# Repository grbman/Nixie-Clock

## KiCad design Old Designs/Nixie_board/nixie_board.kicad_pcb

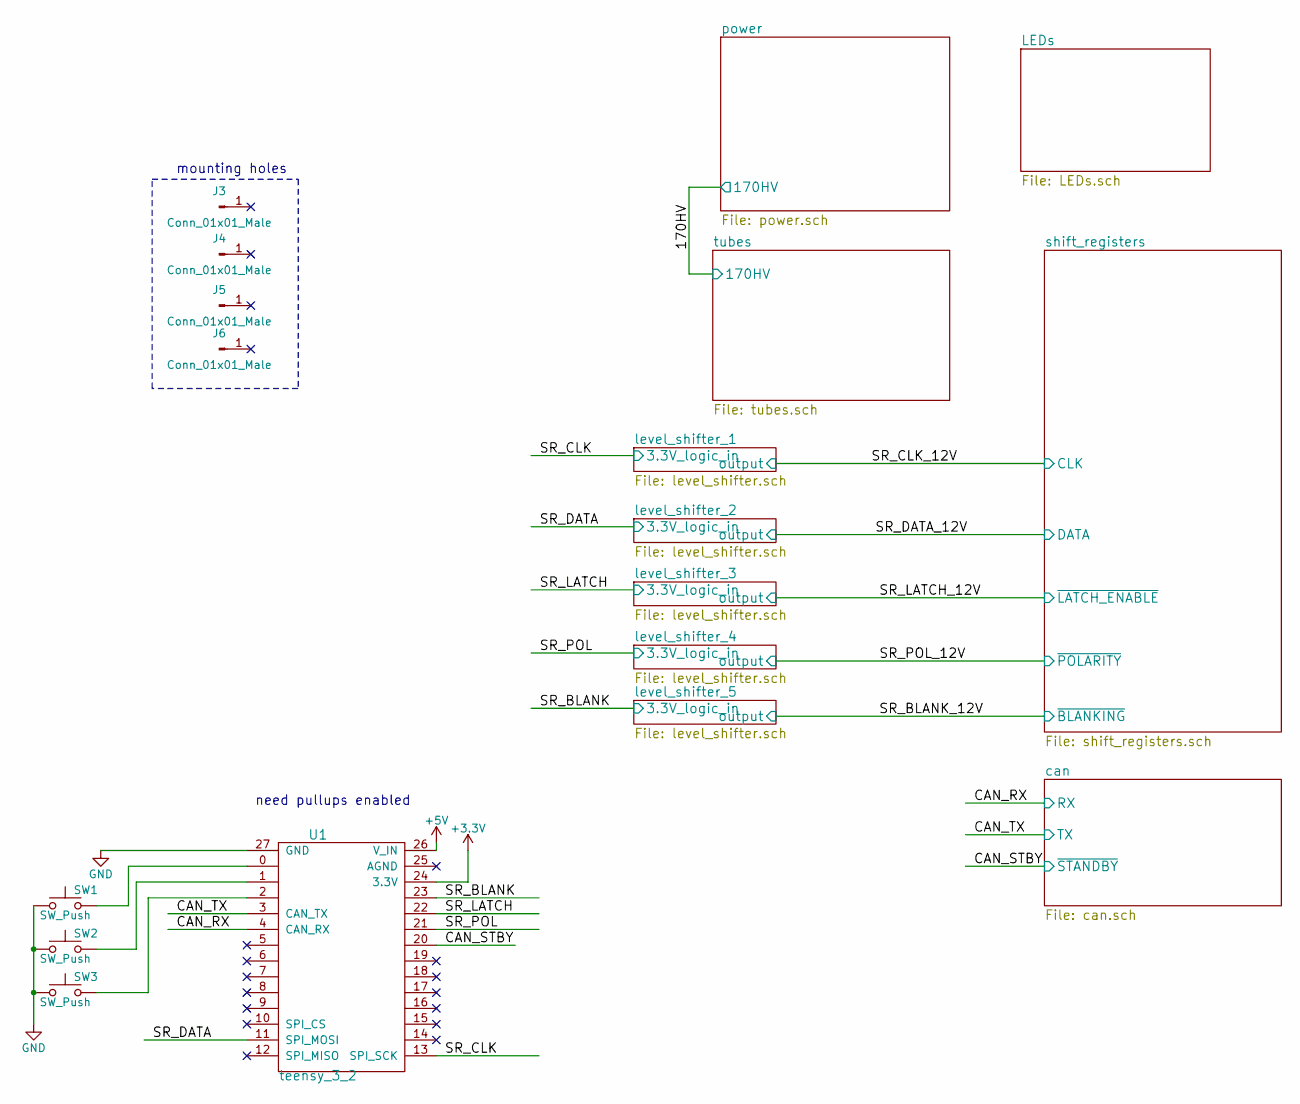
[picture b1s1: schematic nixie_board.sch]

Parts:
J3, J4, J5, J6: Conn_01x01_Male; MountingHole_3.2mm_M3_DIN965_Pad
SW1, SW2, SW3: SW_Push; SW_PUSH_6mm
U1: teensy_3_2; teensy_3.2

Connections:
+3V3: U1.24 (3.3V); also elsewhere on the board
+5V: U1.26 (V_IN); also elsewhere on the board
/CAN_RX: U1.4 (CAN_RX); also elsewhere on the board
/CAN_STBY: U1.20; also elsewhere on the board
/CAN_TX: U1.3 (CAN_TX); also elsewhere on the board
/SR_BLANK: U1.23; also elsewhere on the board
/SR_CLK: U1.13 (SPI_SCK); also elsewhere on the board
/SR_DATA: U1.11 (SPI_MOSI); also elsewhere on the board
/SR_LATCH: U1.22; also elsewhere on the board
/SR_POL: U1.21; also elsewhere on the board
GND: SW1.1, SW2.1, SW3.1, U1.27 (GND); also elsewhere on the board
unnamed: SW1.2, U1.0
unnamed: SW2.2, U1.1
unnamed: SW3.2, U1.2

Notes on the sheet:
need pullups enabled
mounting holes

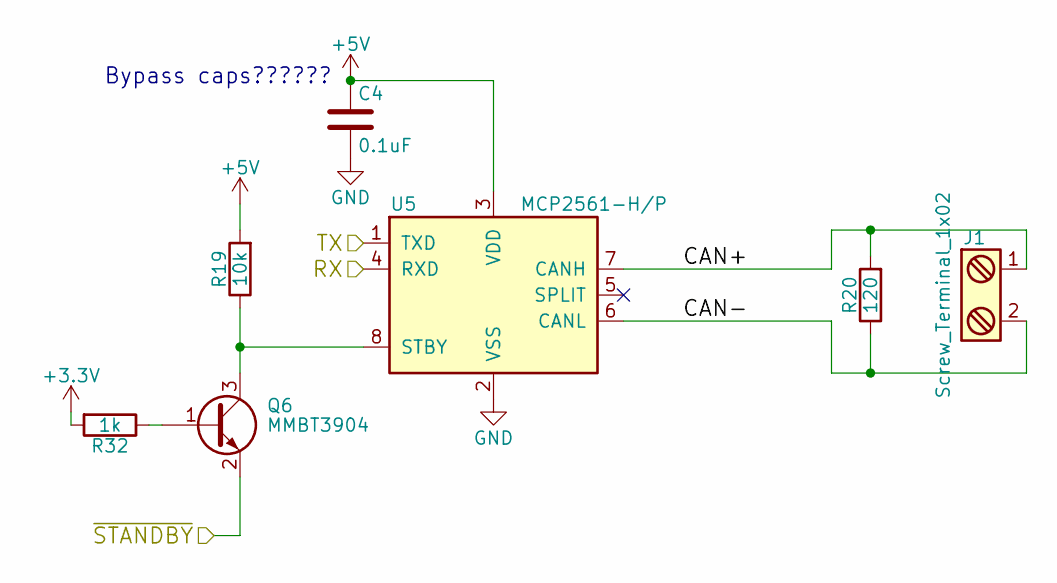
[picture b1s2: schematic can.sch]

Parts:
C4: 0.1uF; C_0603_HandSoldering
J1: Screw_Terminal_1x02; TerminalBlock_Pheonix_PT-3.5mm_2pol
Q6: MMBT3904; SOT-23
R19: 10k; R_0603_HandSoldering
R20: 120; R_0603_HandSoldering
R32: 1k; R_0603_HandSoldering
U5: MCP2561-H/P; DIP-8_W7.62mm

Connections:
+3V3: R32.2; also elsewhere on the board
+5V: C4.1, R19.2, U5.3 (VDD); also elsewhere on the board
/CAN_RX: U5.4 (RXD); also elsewhere on the board
/CAN_STBY: Q6.2 (E); also elsewhere on the board
/CAN_TX: U5.1 (TXD); also elsewhere on the board
/can/CAN+: J1.1, R20.2, U5.7 (CANH)
/can/CAN-: J1.2, R20.1, U5.6 (CANL)
GND: C4.2, U5.2 (VSS); also elsewhere on the board
unnamed: Q6.1 (B), R32.1
unnamed: Q6.3 (C), R19.1, U5.8 (STBY)

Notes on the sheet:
Bypass caps??????

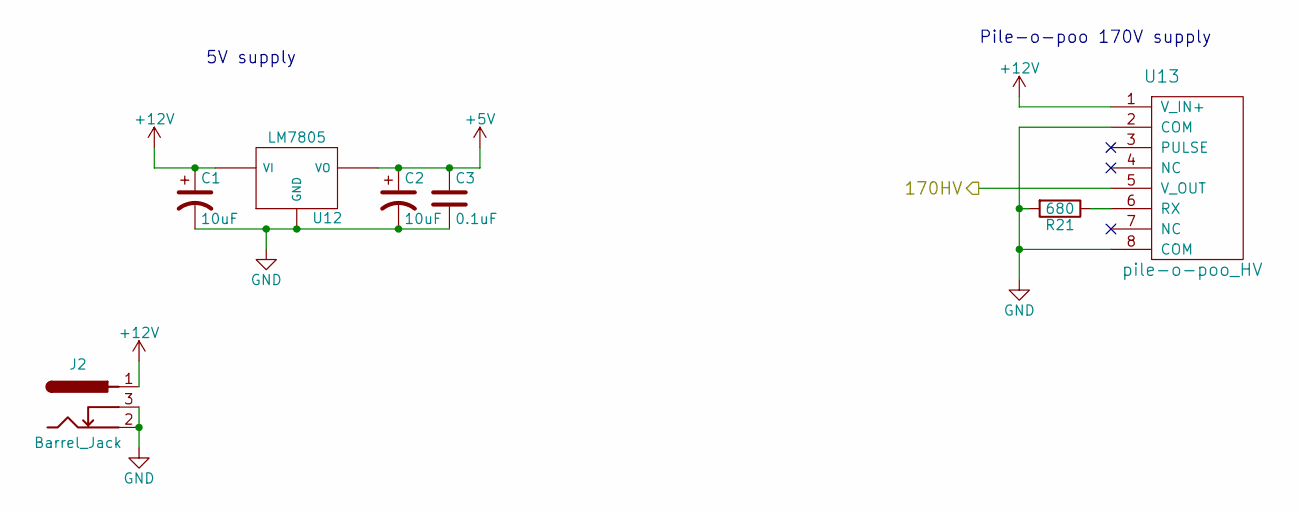
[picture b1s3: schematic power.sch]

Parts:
C1, C2: 10uF; CP_Radial_D5.0mm_P2.00mm
C3: 0.1uF; C_0603_HandSoldering
J2: Barrel_Jack; barrel_jack
R21: 680; R_0603_HandSoldering
U12: LM7805; TO-220
U13: pile-o-poo_HV; pile_o_poo

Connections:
+5V: C2.1, C3.1, U12.3 (VO); also elsewhere on the board
+12V: C1.1, J2.1, U12.1 (VI), U13.1 (V_IN+); also elsewhere on the board
/170HV: U13.5 (V_OUT); also elsewhere on the board
GND: C1.2, C2.2, C3.2, J2.2, J2.3, R21.2, U12.2 (GND), U13.2 (COM), U13.8 (COM); also elsewhere on the board
unnamed: R21.1, U13.6 (RX)

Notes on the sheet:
5V supply
Pile-o-poo 170V supply

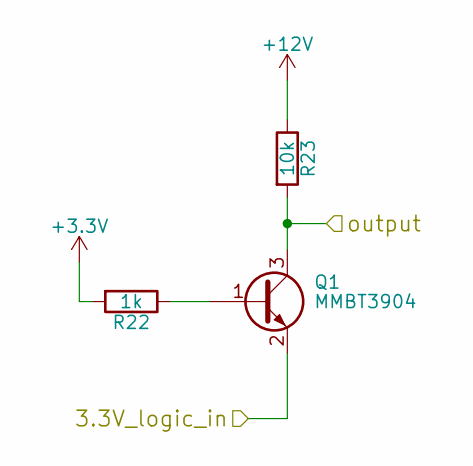
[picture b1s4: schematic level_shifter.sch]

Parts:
Q4: MMBT3904; SOT-23
R24: 1k; R_0603_HandSoldering
R25: 10k; R_0603_HandSoldering

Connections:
+3V3: R24.2; also elsewhere on the board
+12V: R25.1; also elsewhere on the board
/SR_POL: Q4.2 (E); also elsewhere on the board

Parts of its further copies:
Q1, Q2, Q3, Q5: MMBT3904; SOT-23
R22, R26, R28, R30: 1k; R_0603_HandSoldering
R23, R27, R29, R31: 10k; R_0603_HandSoldering

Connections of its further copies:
+3V3: R22.2, R26.2, R28.2, R30.2; also elsewhere on the board
+12V: R23.1, R27.1, R29.1, R31.1; also elsewhere on the board
/SR_BLANK: Q5.2 (E); also elsewhere on the board
/SR_BLANK_12V: Q5.3 (C), R31.2; also elsewhere on the board
/SR_CLK: Q1.2 (E); also elsewhere on the board
/SR_CLK_12V: Q1.3 (C), R23.2; also elsewhere on the board
/SR_DATA: Q2.2 (E); also elsewhere on the board
/SR_LATCH: Q3.2 (E); also elsewhere on the board
/SR_LATCH_12V: Q3.3 (C), R27.2; also elsewhere on the board
unnamed: Q1.1 (B), R22.1
unnamed: Q3.1 (B), R26.1
unnamed: Q5.1 (B), R30.1

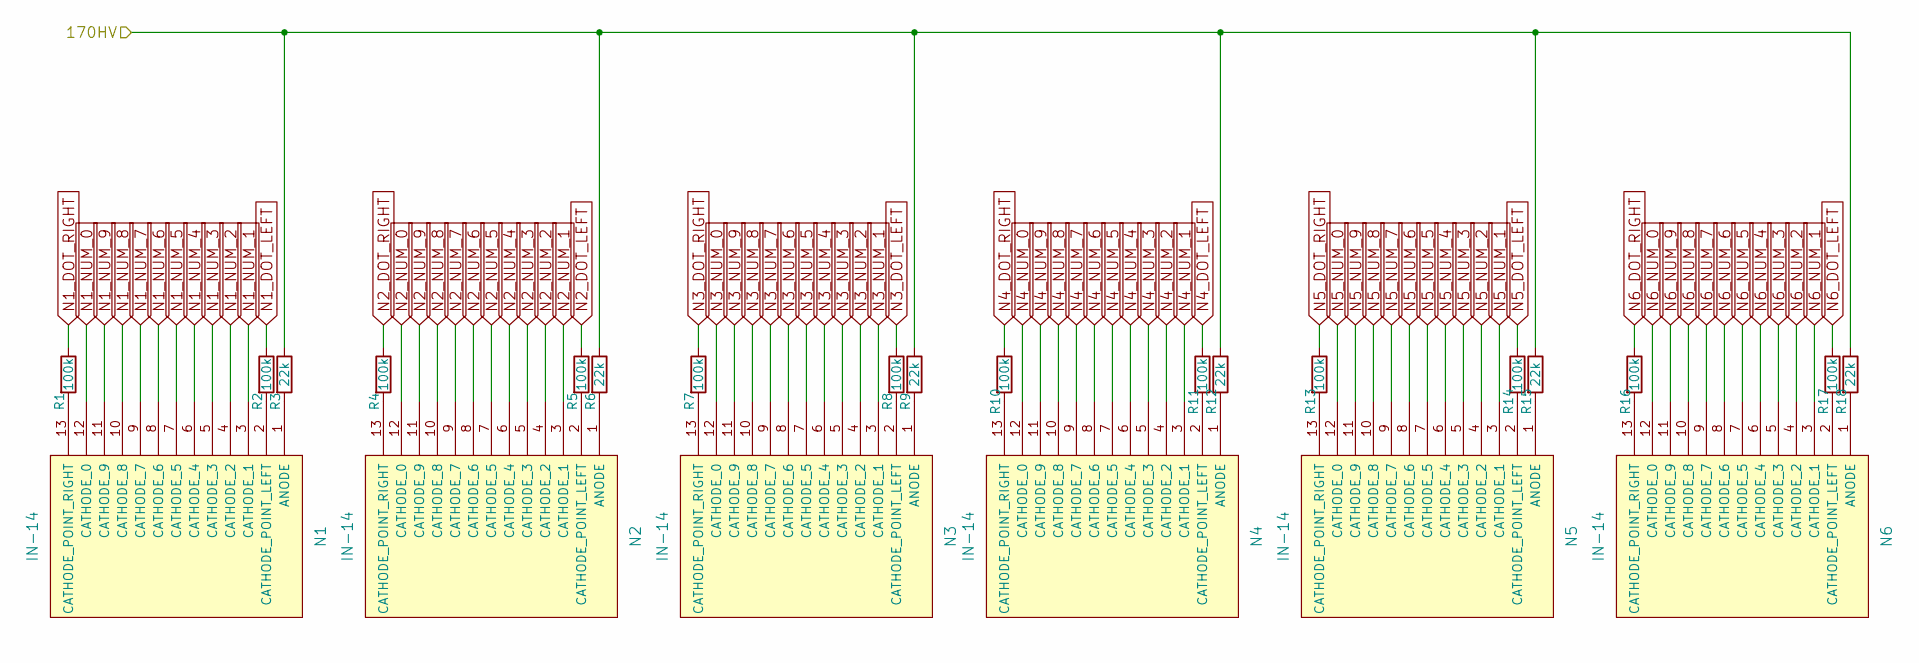
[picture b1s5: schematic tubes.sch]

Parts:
N1, N2, N3, N4, N5, N6: IN-14; in-14
R1, R2, R4, R5, R7, R8, R10, R11, R13, R14, R16, R17: 100k; R_0603_HandSoldering
R3, R6, R9, R12, R15, R18: 22k; R_0603_HandSoldering

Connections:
/170HV: R3.1, R6.1, R9.1, R12.1, R15.1, R18.1; also elsewhere on the board
N1_DOT_LEFT: R2.1; also elsewhere on the board
N1_DOT_RIGHT: R1.1; also elsewhere on the board
N1_NUM_0: N1.12 (CATHODE_0); also elsewhere on the board
N1_NUM_1: N1.3 (CATHODE_1); also elsewhere on the board
N1_NUM_2: N1.4 (CATHODE_2); also elsewhere on the board
N1_NUM_3: N1.5 (CATHODE_3); also elsewhere on the board
N1_NUM_4: N1.6 (CATHODE_4); also elsewhere on the board
N1_NUM_5: N1.7 (CATHODE_5); also elsewhere on the board
N1_NUM_6: N1.8 (CATHODE_6); also elsewhere on the board
N1_NUM_7: N1.9 (CATHODE_7); also elsewhere on the board
N1_NUM_8: N1.10 (CATHODE_8); also elsewhere on the board
N1_NUM_9: N1.11 (CATHODE_9); also elsewhere on the board
N2_DOT_LEFT: R5.1; also elsewhere on the board
N2_DOT_RIGHT: R4.1; also elsewhere on the board
N2_NUM_0: N2.12 (CATHODE_0); also elsewhere on the board
N2_NUM_1: N2.3 (CATHODE_1); also elsewhere on the board
N2_NUM_2: N2.4 (CATHODE_2); also elsewhere on the board
N2_NUM_3: N2.5 (CATHODE_3); also elsewhere on the board
N2_NUM_4: N2.6 (CATHODE_4); also elsewhere on the board
N2_NUM_5: N2.7 (CATHODE_5); also elsewhere on the board
N2_NUM_6: N2.8 (CATHODE_6); also elsewhere on the board
N2_NUM_7: N2.9 (CATHODE_7); also elsewhere on the board
N2_NUM_8: N2.10 (CATHODE_8); also elsewhere on the board
N2_NUM_9: N2.11 (CATHODE_9); also elsewhere on the board
N3_DOT_LEFT: R8.1; also elsewhere on the board
N3_DOT_RIGHT: R7.1; also elsewhere on the board
N3_NUM_0: N3.12 (CATHODE_0); also elsewhere on the board
N3_NUM_1: N3.3 (CATHODE_1); also elsewhere on the board
N3_NUM_2: N3.4 (CATHODE_2); also elsewhere on the board
N3_NUM_3: N3.5 (CATHODE_3); also elsewhere on the board
N3_NUM_4: N3.6 (CATHODE_4); also elsewhere on the board
N3_NUM_5: N3.7 (CATHODE_5); also elsewhere on the board
N3_NUM_6: N3.8 (CATHODE_6); also elsewhere on the board
N3_NUM_7: N3.9 (CATHODE_7); also elsewhere on the board
N3_NUM_8: N3.10 (CATHODE_8); also elsewhere on the board
N3_NUM_9: N3.11 (CATHODE_9); also elsewhere on the board
N4_DOT_LEFT: R11.1; also elsewhere on the board
N4_DOT_RIGHT: R10.1; also elsewhere on the board
N4_NUM_0: N4.12 (CATHODE_0); also elsewhere on the board
N4_NUM_1: N4.3 (CATHODE_1); also elsewhere on the board
N4_NUM_2: N4.4 (CATHODE_2); also elsewhere on the board
N4_NUM_3: N4.5 (CATHODE_3); also elsewhere on the board
N4_NUM_4: N4.6 (CATHODE_4); also elsewhere on the board
N4_NUM_5: N4.7 (CATHODE_5); also elsewhere on the board
N4_NUM_6: N4.8 (CATHODE_6); also elsewhere on the board
N4_NUM_7: N4.9 (CATHODE_7); also elsewhere on the board
N4_NUM_8: N4.10 (CATHODE_8); also elsewhere on the board
N4_NUM_9: N4.11 (CATHODE_9); also elsewhere on the board
N5_DOT_LEFT: R14.1; also elsewhere on the board
N5_DOT_RIGHT: R13.1; also elsewhere on the board
N5_NUM_0: N5.12 (CATHODE_0); also elsewhere on the board
N5_NUM_1: N5.3 (CATHODE_1); also elsewhere on the board
N5_NUM_2: N5.4 (CATHODE_2); also elsewhere on the board
N5_NUM_3: N5.5 (CATHODE_3); also elsewhere on the board
N5_NUM_4: N5.6 (CATHODE_4); also elsewhere on the board
N5_NUM_5: N5.7 (CATHODE_5); also elsewhere on the board
N5_NUM_6: N5.8 (CATHODE_6); also elsewhere on the board
N5_NUM_7: N5.9 (CATHODE_7); also elsewhere on the board
N5_NUM_8: N5.10 (CATHODE_8); also elsewhere on the board
N5_NUM_9: N5.11 (CATHODE_9); also elsewhere on the board
N6_DOT_LEFT: R17.1; also elsewhere on the board
N6_DOT_RIGHT: R16.1; also elsewhere on the board
N6_NUM_0: N6.12 (CATHODE_0); also elsewhere on the board
N6_NUM_1: N6.3 (CATHODE_1); also elsewhere on the board
N6_NUM_2: N6.4 (CATHODE_2); also elsewhere on the board
N6_NUM_3: N6.5 (CATHODE_3); also elsewhere on the board
N6_NUM_4: N6.6 (CATHODE_4); also elsewhere on the board
N6_NUM_5: N6.7 (CATHODE_5); also elsewhere on the board
N6_NUM_6: N6.8 (CATHODE_6); also elsewhere on the board
N6_NUM_7: N6.9 (CATHODE_7); also elsewhere on the board
N6_NUM_8: N6.10 (CATHODE_8); also elsewhere on the board
N6_NUM_9: N6.11 (CATHODE_9); also elsewhere on the board
unnamed: N1.1 (ANODE), R3.2
unnamed: N1.2 (CATHODE_POINT_LEFT), R2.2
unnamed: N1.13 (CATHODE_POINT_RIGHT), R1.2
unnamed: N2.1 (ANODE), R6.2
unnamed: N2.2 (CATHODE_POINT_LEFT), R5.2
unnamed: N2.13 (CATHODE_POINT_RIGHT), R4.2
unnamed: N3.1 (ANODE), R9.2
unnamed: N3.2 (CATHODE_POINT_LEFT), R8.2
unnamed: N3.13 (CATHODE_POINT_RIGHT), R7.2
unnamed: N4.1 (ANODE), R12.2
unnamed: N4.2 (CATHODE_POINT_LEFT), R11.2
unnamed: N4.13 (CATHODE_POINT_RIGHT), R10.2
unnamed: N5.1 (ANODE), R15.2
unnamed: N5.2 (CATHODE_POINT_LEFT), R14.2
unnamed: N5.13 (CATHODE_POINT_RIGHT), R13.2
unnamed: N6.1 (ANODE), R18.2
unnamed: N6.2 (CATHODE_POINT_LEFT), R17.2
unnamed: N6.13 (CATHODE_POINT_RIGHT), R16.2

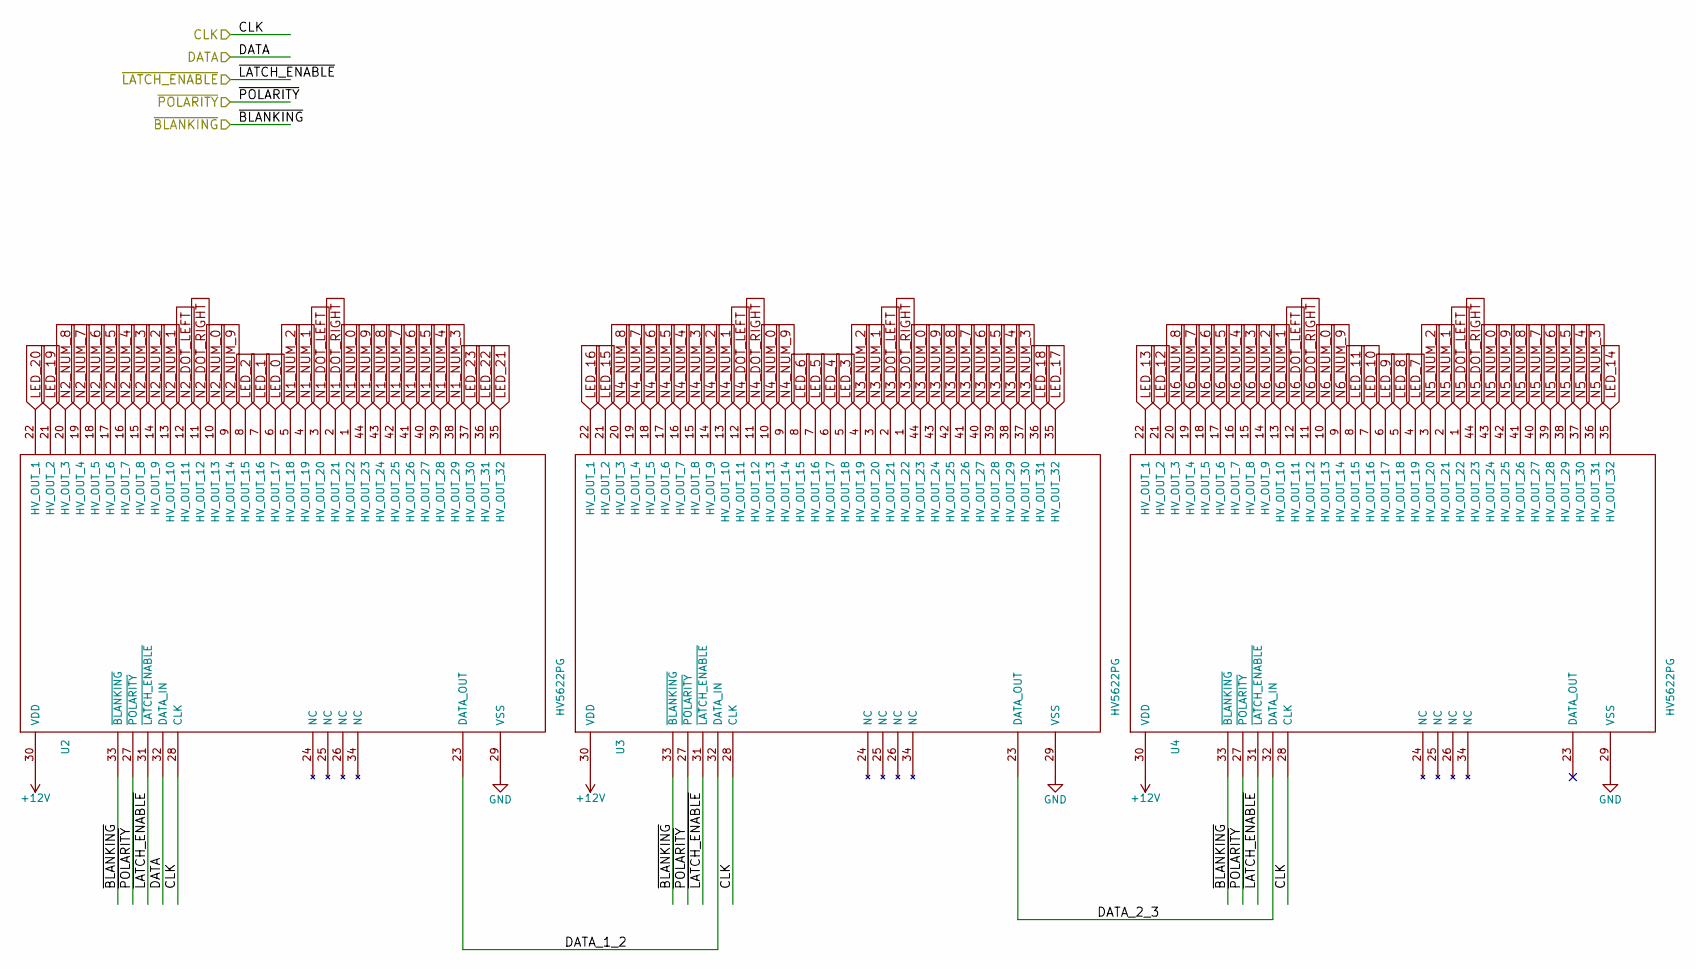
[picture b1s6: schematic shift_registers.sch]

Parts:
U2, U3, U4: HV5622PG; LQFP-44_Gullwing

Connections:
+12V: U2.30 (VDD), U3.30 (VDD), U4.30 (VDD); also elsewhere on the board
/SR_BLANK_12V: U2.33 (~BLANKING), U3.33 (~BLANKING), U4.33 (~BLANKING); also elsewhere on the board
/SR_CLK_12V: U2.28 (CLK), U3.28 (CLK), U4.28 (CLK); also elsewhere on the board
/SR_LATCH_12V: U2.31 (~LATCH_ENABLE), U3.31 (~LATCH_ENABLE), U4.31 (~LATCH_ENABLE); also elsewhere on the board
/shift_registers/DATA_1_2: U2.23 (DATA_OUT), U3.32 (DATA_IN)
/shift_registers/DATA_2_3: U3.23 (DATA_OUT), U4.32 (DATA_IN)
GND: U2.29 (VSS), U3.29 (VSS), U4.29 (VSS); also elsewhere on the board
LED_0: U2.6 (HV_OUT_17); also elsewhere on the board
LED_1: U2.7 (HV_OUT_16); also elsewhere on the board
LED_2: U2.8 (HV_OUT_15); also elsewhere on the board
LED_3: U3.5 (HV_OUT_18); also elsewhere on the board
LED_4: U3.6 (HV_OUT_17); also elsewhere on the board
LED_5: U3.7 (HV_OUT_16); also elsewhere on the board
LED_6: U3.8 (HV_OUT_15); also elsewhere on the board
LED_7: U4.4 (HV_OUT_19); also elsewhere on the board
LED_8: U4.5 (HV_OUT_18); also elsewhere on the board
LED_9: U4.6 (HV_OUT_17); also elsewhere on the board
LED_10: U4.7 (HV_OUT_16); also elsewhere on the board
LED_11: U4.8 (HV_OUT_15); also elsewhere on the board
LED_12: U4.21 (HV_OUT_2); also elsewhere on the board
LED_13: U4.22 (HV_OUT_1); also elsewhere on the board
LED_14: U4.35 (HV_OUT_32); also elsewhere on the board
LED_15: U3.21 (HV_OUT_2); also elsewhere on the board
LED_16: U3.22 (HV_OUT_1); also elsewhere on the board
LED_17: U3.35 (HV_OUT_32); also elsewhere on the board
LED_18: U3.36 (HV_OUT_31); also elsewhere on the board
LED_19: U2.21 (HV_OUT_2); also elsewhere on the board
LED_20: U2.22 (HV_OUT_1); also elsewhere on the board
LED_21: U2.35 (HV_OUT_32); also elsewhere on the board
LED_22: U2.36 (HV_OUT_31); also elsewhere on the board
LED_23: U2.37 (HV_OUT_30); also elsewhere on the board
N1_DOT_LEFT: U2.3 (HV_OUT_20); also elsewhere on the board
N1_DOT_RIGHT: U2.2 (HV_OUT_21); also elsewhere on the board
N1_NUM_0: U2.1 (HV_OUT_22); also elsewhere on the board
N1_NUM_1: U2.4 (HV_OUT_19); also elsewhere on the board
N1_NUM_2: U2.5 (HV_OUT_18); also elsewhere on the board
N1_NUM_3: U2.38 (HV_OUT_29); also elsewhere on the board
N1_NUM_4: U2.39 (HV_OUT_28); also elsewhere on the board
N1_NUM_5: U2.40 (HV_OUT_27); also elsewhere on the board
N1_NUM_6: U2.41 (HV_OUT_26); also elsewhere on the board
N1_NUM_7: U2.42 (HV_OUT_25); also elsewhere on the board
N1_NUM_8: U2.43 (HV_OUT_24); also elsewhere on the board
N1_NUM_9: U2.44 (HV_OUT_23); also elsewhere on the board
N2_DOT_LEFT: U2.12 (HV_OUT_11); also elsewhere on the board
N2_DOT_RIGHT: U2.11 (HV_OUT_12); also elsewhere on the board
N2_NUM_0: U2.10 (HV_OUT_13); also elsewhere on the board
N2_NUM_1: U2.13 (HV_OUT_10); also elsewhere on the board
N2_NUM_2: U2.14 (HV_OUT_9); also elsewhere on the board
N2_NUM_3: U2.15 (HV_OUT_8); also elsewhere on the board
N2_NUM_4: U2.16 (HV_OUT_7); also elsewhere on the board
N2_NUM_5: U2.17 (HV_OUT_6); also elsewhere on the board
N2_NUM_6: U2.18 (HV_OUT_5); also elsewhere on the board
N2_NUM_7: U2.19 (HV_OUT_4); also elsewhere on the board
N2_NUM_8: U2.20 (HV_OUT_3); also elsewhere on the board
N2_NUM_9: U2.9 (HV_OUT_14); also elsewhere on the board
N3_DOT_LEFT: U3.2 (HV_OUT_21); also elsewhere on the board
N3_DOT_RIGHT: U3.1 (HV_OUT_22); also elsewhere on the board
N3_NUM_0: U3.44 (HV_OUT_23); also elsewhere on the board
N3_NUM_1: U3.3 (HV_OUT_20); also elsewhere on the board
N3_NUM_2: U3.4 (HV_OUT_19); also elsewhere on the board
N3_NUM_3: U3.37 (HV_OUT_30); also elsewhere on the board
N3_NUM_4: U3.38 (HV_OUT_29); also elsewhere on the board
N3_NUM_5: U3.39 (HV_OUT_28); also elsewhere on the board
N3_NUM_6: U3.40 (HV_OUT_27); also elsewhere on the board
N3_NUM_7: U3.41 (HV_OUT_26); also elsewhere on the board
N3_NUM_8: U3.42 (HV_OUT_25); also elsewhere on the board
N3_NUM_9: U3.43 (HV_OUT_24); also elsewhere on the board
N4_DOT_LEFT: U3.12 (HV_OUT_11); also elsewhere on the board
N4_DOT_RIGHT: U3.11 (HV_OUT_12); also elsewhere on the board
N4_NUM_0: U3.10 (HV_OUT_13); also elsewhere on the board
N4_NUM_1: U3.13 (HV_OUT_10); also elsewhere on the board
N4_NUM_2: U3.14 (HV_OUT_9); also elsewhere on the board
N4_NUM_3: U3.15 (HV_OUT_8); also elsewhere on the board
N4_NUM_4: U3.16 (HV_OUT_7); also elsewhere on the board
N4_NUM_5: U3.17 (HV_OUT_6); also elsewhere on the board
N4_NUM_6: U3.18 (HV_OUT_5); also elsewhere on the board
N4_NUM_7: U3.19 (HV_OUT_4); also elsewhere on the board
N4_NUM_8: U3.20 (HV_OUT_3); also elsewhere on the board
N4_NUM_9: U3.9 (HV_OUT_14); also elsewhere on the board
N5_DOT_LEFT: U4.1 (HV_OUT_22); also elsewhere on the board
N5_DOT_RIGHT: U4.44 (HV_OUT_23); also elsewhere on the board
N5_NUM_0: U4.43 (HV_OUT_24); also elsewhere on the board
N5_NUM_1: U4.2 (HV_OUT_21); also elsewhere on the board
N5_NUM_2: U4.3 (HV_OUT_20); also elsewhere on the board
N5_NUM_3: U4.36 (HV_OUT_31); also elsewhere on the board
N5_NUM_4: U4.37 (HV_OUT_30); also elsewhere on the board
N5_NUM_5: U4.38 (HV_OUT_29); also elsewhere on the board
N5_NUM_6: U4.39 (HV_OUT_28); also elsewhere on the board
N5_NUM_7: U4.40 (HV_OUT_27); also elsewhere on the board
N5_NUM_8: U4.41 (HV_OUT_26); also elsewhere on the board
N5_NUM_9: U4.42 (HV_OUT_25); also elsewhere on the board
N6_DOT_LEFT: U4.12 (HV_OUT_11); also elsewhere on the board
N6_DOT_RIGHT: U4.11 (HV_OUT_12); also elsewhere on the board
N6_NUM_0: U4.10 (HV_OUT_13); also elsewhere on the board
N6_NUM_1: U4.13 (HV_OUT_10); also elsewhere on the board
N6_NUM_2: U4.14 (HV_OUT_9); also elsewhere on the board
N6_NUM_3: U4.15 (HV_OUT_8); also elsewhere on the board
N6_NUM_4: U4.16 (HV_OUT_7); also elsewhere on the board
N6_NUM_5: U4.17 (HV_OUT_6); also elsewhere on the board
N6_NUM_6: U4.18 (HV_OUT_5); also elsewhere on the board
N6_NUM_7: U4.19 (HV_OUT_4); also elsewhere on the board
N6_NUM_8: U4.20 (HV_OUT_3); also elsewhere on the board
N6_NUM_9: U4.9 (HV_OUT_14); also elsewhere on the board

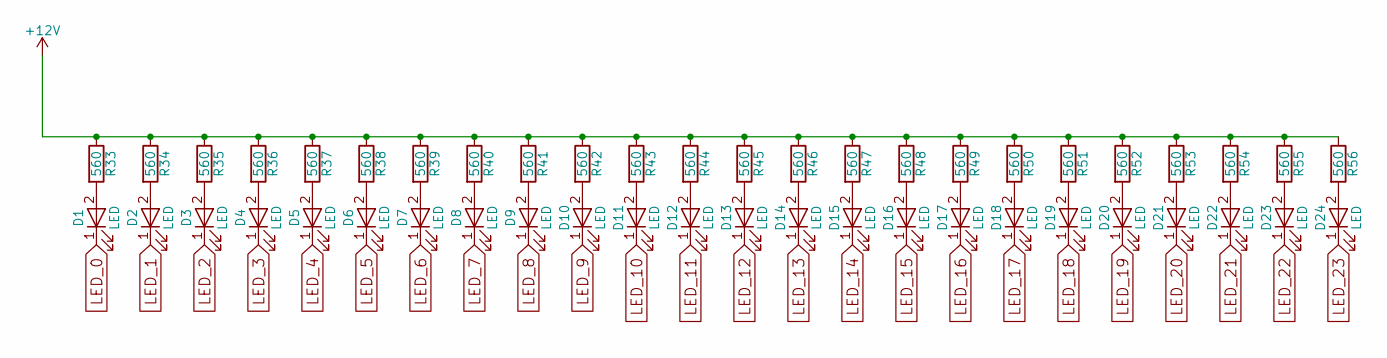
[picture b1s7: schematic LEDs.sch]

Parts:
D1, D2, D3, D4, D5, D6, D7, D8, D9, D10, D11, D12, D13, D14, D15, D16, D17, D18, D19, D20, D21, D22, D23, D24: LED; LED_0603_HandSoldering
R33, R34, R35, R36, R37, R38, R39, R40, R41, R42, R43, R44, R45, R46, R47, R48, R49, R50, R51, R52, R53, R54, R55, R56: 560; R_0603_HandSoldering

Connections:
+12V: R33.1, R34.1, R35.1, R36.1, R37.1, R38.1, R39.1, R40.1, R41.1, R42.1, R43.1, R44.1, R45.1, R46.1, R47.1, R48.1, R49.1, R50.1, R51.1, R52.1, R53.1, R54.1, R55.1, R56.1; also elsewhere on the board
LED_0: D1.1 (K); also elsewhere on the board
LED_1: D2.1 (K); also elsewhere on the board
LED_2: D3.1 (K); also elsewhere on the board
LED_3: D4.1 (K); also elsewhere on the board
LED_4: D5.1 (K); also elsewhere on the board
LED_5: D6.1 (K); also elsewhere on the board
LED_6: D7.1 (K); also elsewhere on the board
LED_7: D8.1 (K); also elsewhere on the board
LED_8: D9.1 (K); also elsewhere on the board
LED_9: D10.1 (K); also elsewhere on the board
LED_10: D11.1 (K); also elsewhere on the board
LED_11: D12.1 (K); also elsewhere on the board
LED_12: D13.1 (K); also elsewhere on the board
LED_13: D14.1 (K); also elsewhere on the board
LED_14: D15.1 (K); also elsewhere on the board
LED_15: D16.1 (K); also elsewhere on the board
LED_16: D17.1 (K); also elsewhere on the board
LED_17: D18.1 (K); also elsewhere on the board
LED_18: D19.1 (K); also elsewhere on the board
LED_19: D20.1 (K); also elsewhere on the board
LED_20: D21.1 (K); also elsewhere on the board
LED_21: D22.1 (K); also elsewhere on the board
LED_22: D23.1 (K); also elsewhere on the board
LED_23: D24.1 (K); also elsewhere on the board
unnamed: D1.2 (A), R33.2
unnamed: D2.2 (A), R34.2
unnamed: D3.2 (A), R35.2
unnamed: D4.2 (A), R36.2
unnamed: D5.2 (A), R37.2
unnamed: D6.2 (A), R38.2
unnamed: D7.2 (A), R39.2
unnamed: D8.2 (A), R40.2
unnamed: D9.2 (A), R41.2
unnamed: D10.2 (A), R42.2
unnamed: D11.2 (A), R43.2
unnamed: D12.2 (A), R44.2
unnamed: D13.2 (A), R45.2
unnamed: D14.2 (A), R46.2
unnamed: D15.2 (A), R47.2
unnamed: D16.2 (A), R48.2
unnamed: D17.2 (A), R49.2
unnamed: D18.2 (A), R50.2
unnamed: D19.2 (A), R51.2
unnamed: D20.2 (A), R52.2
unnamed: D21.2 (A), R53.2
unnamed: D22.2 (A), R54.2
unnamed: D23.2 (A), R55.2
unnamed: D24.2 (A), R56.2

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
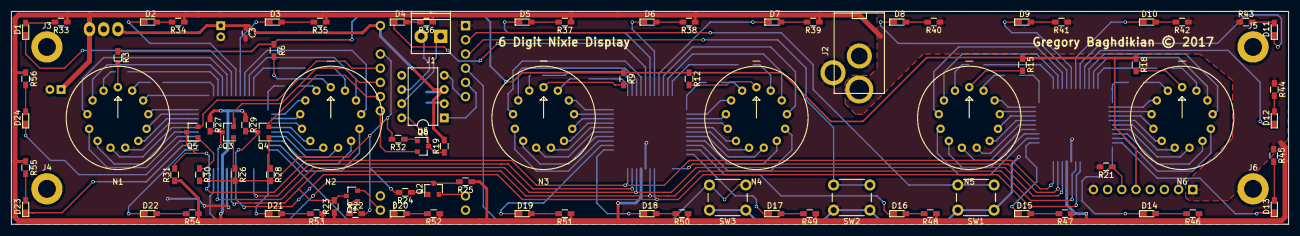
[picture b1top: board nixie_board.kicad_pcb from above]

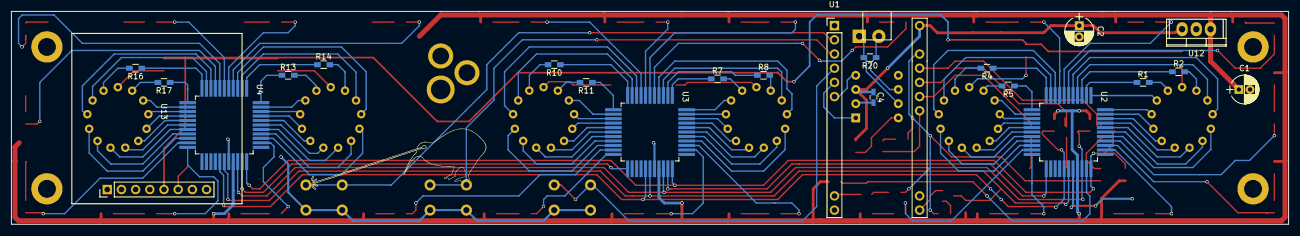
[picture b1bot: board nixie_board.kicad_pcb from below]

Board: 2 copper layers, 228.6 x 38.1 mm, 112 parts (22 on the bottom side), 171 nets.

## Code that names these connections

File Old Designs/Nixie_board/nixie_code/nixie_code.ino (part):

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boolean stringComplete = false;

/* button definitions */
int sr_pol = 21;
int sr_latch = 22;
int sr_blank = 23;
int button0 = 0;
int button1 = 1;
int button2 = 2;
int can_stby = 20;
int alt_miso = 12;
int wifi_en = 6;

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
void setup() {
  // put your setup code here, to run once:
  sr_data[0] = 0;
  sr_data[1] = 0;
  sr_data[2] = 0;
  //sr_data_prev[0] = 1;
  //sr_data_prev[1] = 1;
  //sr_data_prev[2] = 1;

  /* set pin IO modes */
  pinMode (sr_pol, OUTPUT);
  pinMode (sr_latch, OUTPUT);
  pinMode (sr_blank, OUTPUT);
  pinMode (button0, INPUT_PULLUP);
  pinMode (button1, INPUT_PULLUP);
  pinMode (button2, INPUT_PULLUP);
  pinMode (can_stby, OUTPUT);
  pinMode(wifi_en, OUTPUT);

  /* set output pins */ 
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
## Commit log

2024-02-04 first commit to github repo
2024-02-04 built out power supplies, added datasheets
2024-02-11 added fet-based level shifter

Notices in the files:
Old Designs/Nixie_board/nixie_board.kicad_pcb:
Gregory Baghdikian © 2017
